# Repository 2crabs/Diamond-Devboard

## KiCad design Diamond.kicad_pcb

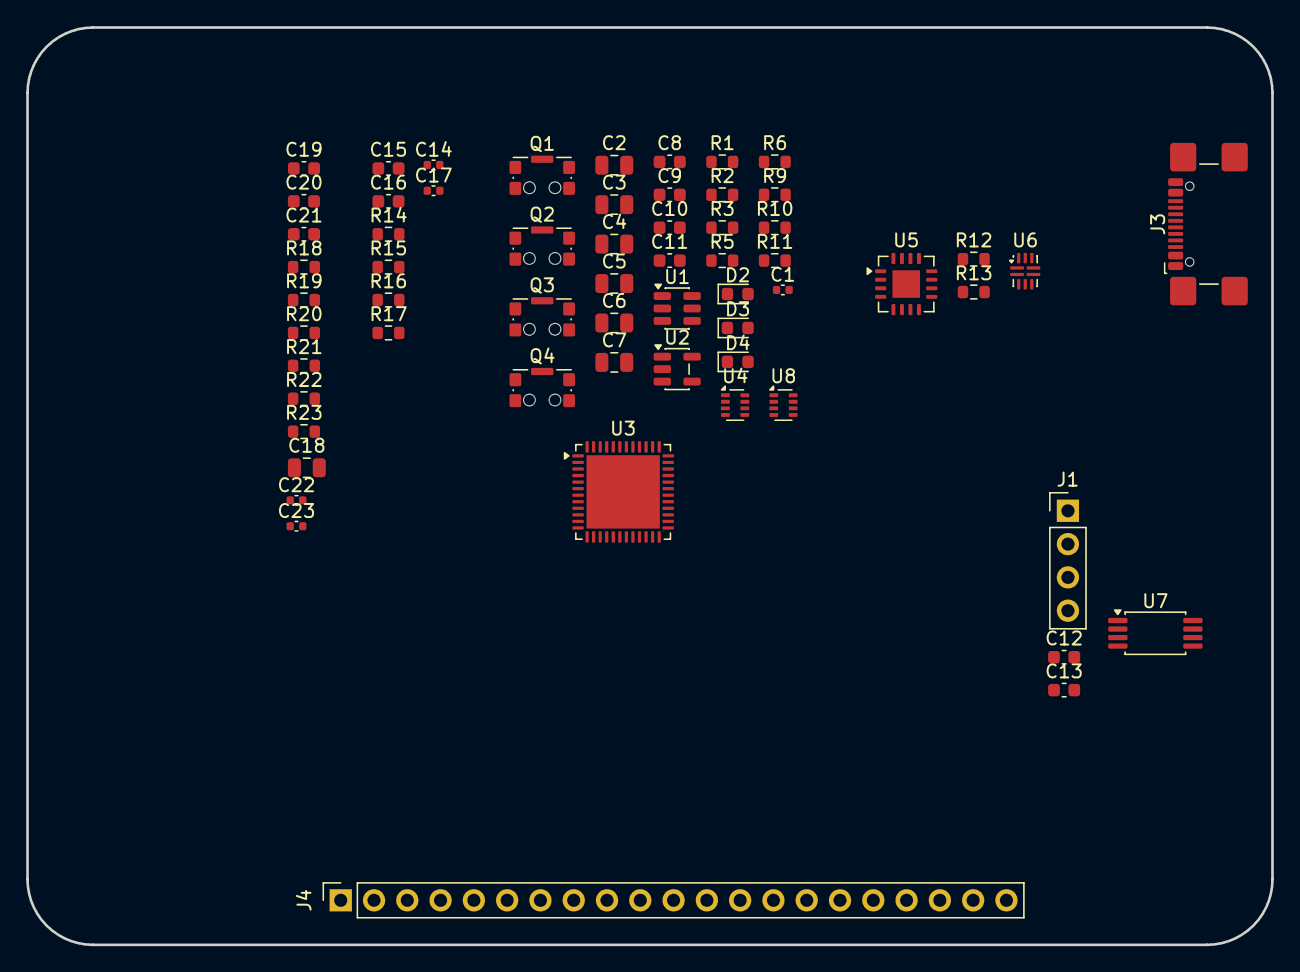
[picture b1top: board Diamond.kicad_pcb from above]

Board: 4 copper layers, 95.0 x 70.0 mm, 61 parts (0 on the bottom side), 29 nets, no tracks yet.

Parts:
C1, C14, C17, C22, C23: 100n; C_0402_1005Metric
C2, C3, C4, C18: 22u; C_0805_2012Metric
C5, C6, C7: 10u; C_0805_2012Metric
C8, C9, C10, C11, C15, C16, C19, C20, C21: 1u; C_0603_1608Metric
C12, C13: 2u2; C_0603_1608Metric
D2, D3, D4: BLU; LED_0603_1608Metric
J1: SWD; PinHeader_1x04_P2.54mm_Vertical
J3: USB_C_Receptacle_USB2.0_16P; USB_C_Receptacle_GCT_USB4110
J4: Conn_01x21_Pin; PinSocket_1x21_P2.54mm_Vertical
Q1, Q2, Q3, Q4: SSD2300; SW_SPST_CK_KMS2xxGP
R1: 2; R_0603_1608Metric
R2, R3, R5, R6, R9, R10, R11, R15: 10k; R_0603_1608Metric
R12, R13, R14: 5k1; R_0603_1608Metric
R16, R17: 27; R_0603_1608Metric
R18, R19, R20, R21, R22, R23: 4k7; R_0603_1608Metric
U1: AP63205WU; TSOT-23-6
U2: AP2112K-3.3; SOT-23-5
U3: STM32H503CBUx; QFN-48-1EP_7x7mm_P0.5mm_EP5.6x5.6mm
U4, U8: TPS2116DRL; SOT-583-8
U5: FT201XQ; QFN-16-1EP_4x4mm_P0.65mm_EP2.1x2.1mm
U6: USB3740B-AI9; UQFN-10_1.6x2.1mm_P0.5mm
U7: 47L16; TSSOP-8_4.4x3mm_P0.65mm

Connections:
+3V3: C10.1, C11.1, C16.1, C19.1, C22.1, C23.1, R18.1, R19.1, R20.1, R21.1, R22.1, U2.5 (VOUT), U3.1 (VBAT), U3.9 (VDDA), U3.24 (VDD), U3.36 (VDD), U3.48 (VDD), U5.1 (VCCIO), U5.9 (~RESET), U7.8 (VCC)
+5V: C8.1, C9.1, C14.1, C15.1, C17.1, R9.1, R10.1, R11.1, U2.1 (VIN), U2.3 (EN), U4.2 (VOUT), U4.7 (VOUT), U5.10 (VCC), U6.5 (VDD)
/Schematic/MCU/BOOT0: C21.1, R23.1, U3.44 (BOOT0)
/Schematic/MCU/RST: C20.1, R22.2, U3.7 (NRST)
/Schematic/MCU/SCL: R20.2, R21.2, U7.6 (SCL)
/Schematic/MCU/SDA: R18.2, R19.2, U7.5 (SDA)
/Schematic/Power/5V_BUCK: C2.1, C3.1, C4.1, R5.1, U1.1 (FB), U8.3 (VIN1), U8.5 (MODE)
/Schematic/Power/ST1: R9.2, U8.8 (ST)
/Schematic/Power/ST2: R10.2, U4.8 (ST)
/Schematic/Power/SWITCH1: U4.6 (VIN2), U8.2 (VOUT), U8.7 (VOUT)
/Schematic/USB C/DM: J3.A7 (D-), J3.B7 (D-), U6.1 (DM_1), U6.9 (DM)
/Schematic/USB C/DM_2: R16.2, U6.7 (DM_2)
/Schematic/USB C/DP: J3.A6 (D+), J3.B6 (D+), U6.2 (DP_1), U6.10 (DP)
/Schematic/USB C/DP_2: R17.2, U6.6 (DP_2)
/Schematic/USB C/VBUS: J3.A4 (VBUS), J3.A9 (VBUS), J3.B4 (VBUS), J3.B9 (VBUS), R2.1, R14.1, U4.3 (VIN1), U4.5 (MODE)
GND: C2.2, C3.2, C4.2, C5.2, C6.2, C7.2, C8.2, C9.2, C10.2, C11.2, C12.2, C13.2, C14.2, C15.2, C16.2, C17.2, C18.2, C19.2, C20.2, C21.2, C22.2, C23.2, J3.A1 (GND), J3.A8 (SBU1), J3.A12 (GND), J3.B1 (GND), J3.B8 (SBU2), J3.B12 (GND), J3.SH (SHIELD), R3.2, R6.2, R12.2, R13.2, R15.2, R23.2, U1.4 (GND), U2.2 (GND), U3.8 (VSSA), U3.23 (VSS), U3.35 (VSS), U3.47 (VSS), U3.49 (VSS), U4.1 (GND), U5.3 (GND), U5.13 (GND), U5.17 (GND), U6.3 (OE_N), U6.8 (GND), U7.2 (A1), U7.3 (A2), U7.4 (VSS), U7.7 (HS), U8.1 (GND)
unnamed: C12.1, U3.46 (VCAP)
unnamed: C13.1, U3.22 (VCAP)
unnamed: J3.A5 (CC1), R13.1
unnamed: J3.B5 (CC2), R12.1
unnamed: C1.1, U1.6 (BST)
unnamed: C5.1, C6.1, C7.1, R1.2, U1.2 (EN), U1.3 (IN)
unnamed: C1.2, U1.5 (SW)
unnamed: R2.2, R3.1, U4.4 (PR1)
unnamed: R14.2, R15.1, U5.4 (CBUS4)
unnamed: R16.1, U5.7 (USBDM)
unnamed: R17.1, U5.6 (USBDP)
unnamed: C18.1, U7.1 (VCAP)
unnamed: R5.2, R6.1, U8.4 (PR1)

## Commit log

2026-05-28 Project files
2026-05-28 Added block diagram
2026-05-28 Removed file
2026-05-29 Added Sheets
2026-05-29 Added power schematic
2026-05-29 Added symbol lib
2026-05-29 Added todos
2026-05-30 Started PCB
